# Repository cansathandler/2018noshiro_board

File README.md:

# 2018noshiro_board
2018年の能代で使用した基板

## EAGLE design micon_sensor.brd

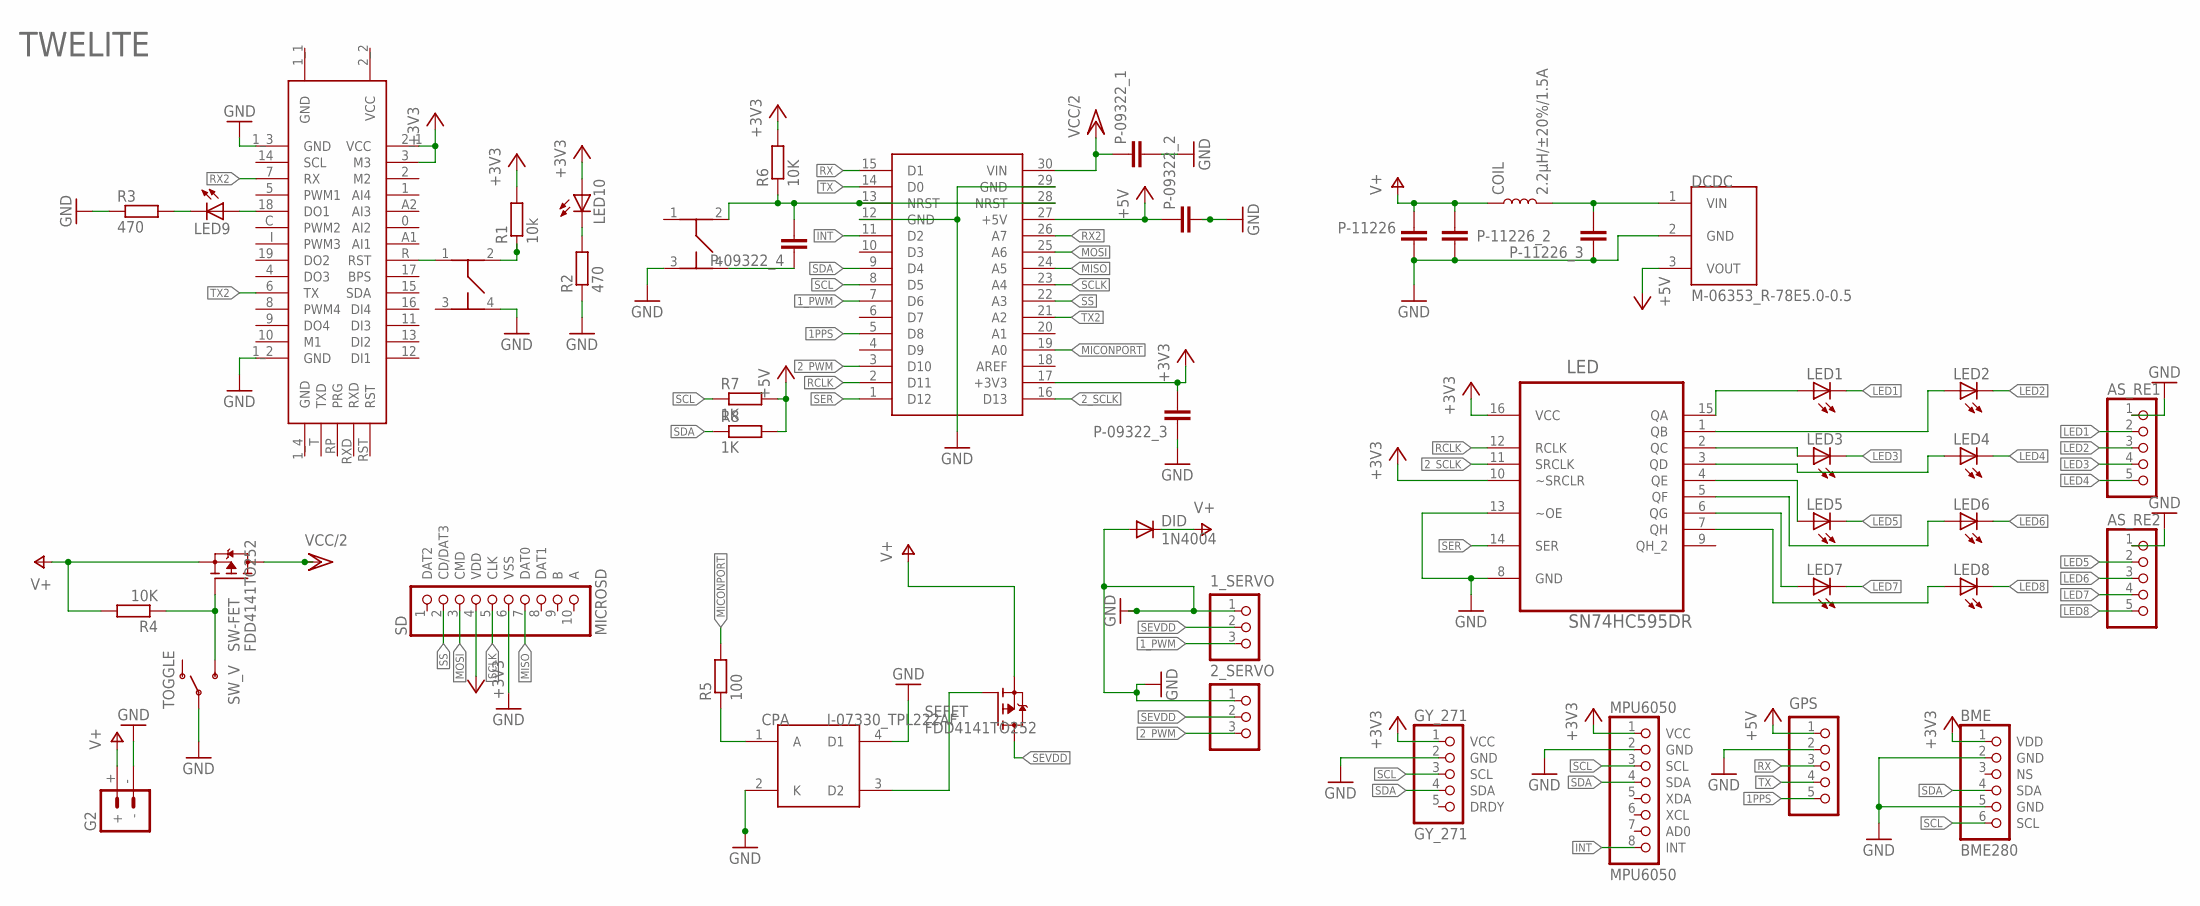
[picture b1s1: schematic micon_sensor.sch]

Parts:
1_SERVO, 2_SERVO: B3B-XH-A
AS_RE1, AS_RE2: PINHD-1X5; 1X05
BME: BME280; 1X06
COIL: 2.2µH/±20%/1.5A; INDUCTOR_2.2UH
CPA: I-07330_TPL222AF; TLP222AF
DCDC: M-06353_R-78E5.0-0.5; R-78E5.0-0.5
DID: 1N4004; DO41-10
G2: BATTERY_CONN_DEANS; DEANS
GPS: B5B-XH-A
GY_271: GY_271; 1X05
LED: SN74HC595DR; SOIC127P600X175-16N
LED1, LED2, LED3, LED4, LED5, LED6, LED7, LED8, LED9, LED10: LEDCHIP-LED0603; CHIP-LED0603
MPU6050: MPU6050; 1X08
P-09322_1, P-09322_2, P-09322_3, P-09322_4, P-11226, P-11226_2, P-11226_3: C-EUC0805; C0805
R1: 10k; R0805
R2, R3: 470; R0805
R4, R6: 10K; R0805
R5: 100; R0805
R7, R8: 1K; R0805
SD: MICROSD; 1X10
SEFET: FDD4141TO252; TO252
SW-FET: FDD4141TO252; TO252
SW_MI: SWITCH
SW_V: TOGGLE; 320-916
TWE_SW: SWITCH
U$1: TWELITE; TWELITE_DIP
U$3: STM32F303K8

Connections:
1PPS: GPS.5, U$3.5 (D8)
1_PWM: 1_SERVO.3, U$3.7 (D6)
2_PWM: 2_SERVO.3, U$3.3 (D10)
2_SCLK: LED.11 (SRCLK), U$3.16 (D13)
+3V3: BME.1 (VDD), GY_271.1 (VCC), LED.10 (~SRCLR), LED.16 (VCC), LED10.A, MPU6050.1 (VCC), P-09322_3.2, R1.2, R6.2, SD.4 (VDD), U$1.2_1 (VCC), U$1.3 (M3), U$3.17 (+3V3)
+5V: DCDC.3 (VOUT), GPS.1, P-09322_2.1, R7.2, R8.2, U$3.27 (+5V)
AREF: U$3.18 (AREF)
GND: 1_SERVO.1, 2_SERVO.1, AS_RE1.1, AS_RE2.1, BME.2 (GND), BME.5 (GND), CPA.2 (K), CPA.4 (D1), DCDC.2 (GND), DID.A, G2.-, GPS.2, GY_271.2 (GND), LED.8 (GND), LED.13 (~OE), MPU6050.2 (GND), P-09322_1.2, P-09322_2.2, P-09322_3.1, P-11226.1, P-11226_2.1, P-11226_3.1, R2.1, R3.1, SD.6 (VSS), SW_MI.3, SW_V.2, TWE_SW.4, U$1.1_2 (GND), U$1.1_3 (GND), U$3.12 (GND), U$3.29 (GND)
INT: MPU6050.8 (INT), U$3.11 (D2)
LED1: AS_RE1.2, LED1.C
LED2: AS_RE1.3, LED2.C
LED3: AS_RE1.4, LED3.C
LED4: AS_RE1.5, LED4.C
LED5: AS_RE2.2, LED5.C
LED6: AS_RE2.3, LED6.C
LED7: AS_RE2.4, LED7.C
LED8: AS_RE2.5, LED8.C
MICONPORT: R5.2, U$3.19 (A0)
MISO: SD.7 (DAT0), U$3.24 (A5)
MOSI: SD.3 (CMD), U$3.25 (A6)
unnamed: COIL.P$2 (2), DCDC.1 (VIN), P-11226_3.2
unnamed: P-09322_4.2, R6.1, SW_MI.2, U$3.13 (NRST), U$3.28 (NRST)
unnamed: P-09322_4.1, SW_MI.4
unnamed: CPA.1 (A), R5.1
unnamed: CPA.3 (D2), SEFET.1 (G)
unnamed: LED.15 (QA), LED1.A
unnamed: LED.1 (QB), LED2.A
unnamed: LED.2 (QC), LED3.A
unnamed: LED.3 (QD), LED4.A
unnamed: LED9.A, U$1.18 (DO1)
unnamed: LED.4 (QE), LED5.A
unnamed: LED.5 (QF), LED6.A
unnamed: LED.6 (QG), LED7.A
unnamed: LED.7 (QH), LED8.A
unnamed: LED9.C, R3.2
unnamed: LED10.C, R2.2
unnamed: TWE_SW.1, U$1.R (RST)
unnamed: R1.1, TWE_SW.2
unnamed: R4.1, SW-FET.1 (G), SW_V.3
RCLK: LED.12 (RCLK), U$3.2 (D11)
RX: GPS.3, U$3.15 (D1)
RX2: U$1.7 (RX), U$3.26 (A7)
SCL: BME.6 (SCL), GY_271.3 (SCL), MPU6050.3 (SCL), R7.1, U$3.8 (D5)
SCLK: SD.5 (CLK), U$3.23 (A4)
SDA: BME.4 (SDA), GY_271.4 (SDA), MPU6050.4 (SDA), R8.1, U$3.9 (D4)
SER: LED.14 (SER), U$3.1 (D12)
SEVDD: 1_SERVO.2, 2_SERVO.2, SEFET.3 (D)
SS: SD.2 (CD/DAT3), U$3.22 (A3)
TX: GPS.4, U$3.14 (D0)
TX2: U$1.6 (TX), U$3.21 (A2)
V+: COIL.P$1 (1), DID.C, G2.+, P-11226.2, P-11226_2.2, R4.2, SEFET.2 (S), SW-FET.2 (S)
VCC/2: P-09322_1.1, SW-FET.3 (D), U$3.30 (VIN)

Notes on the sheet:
TWELITE

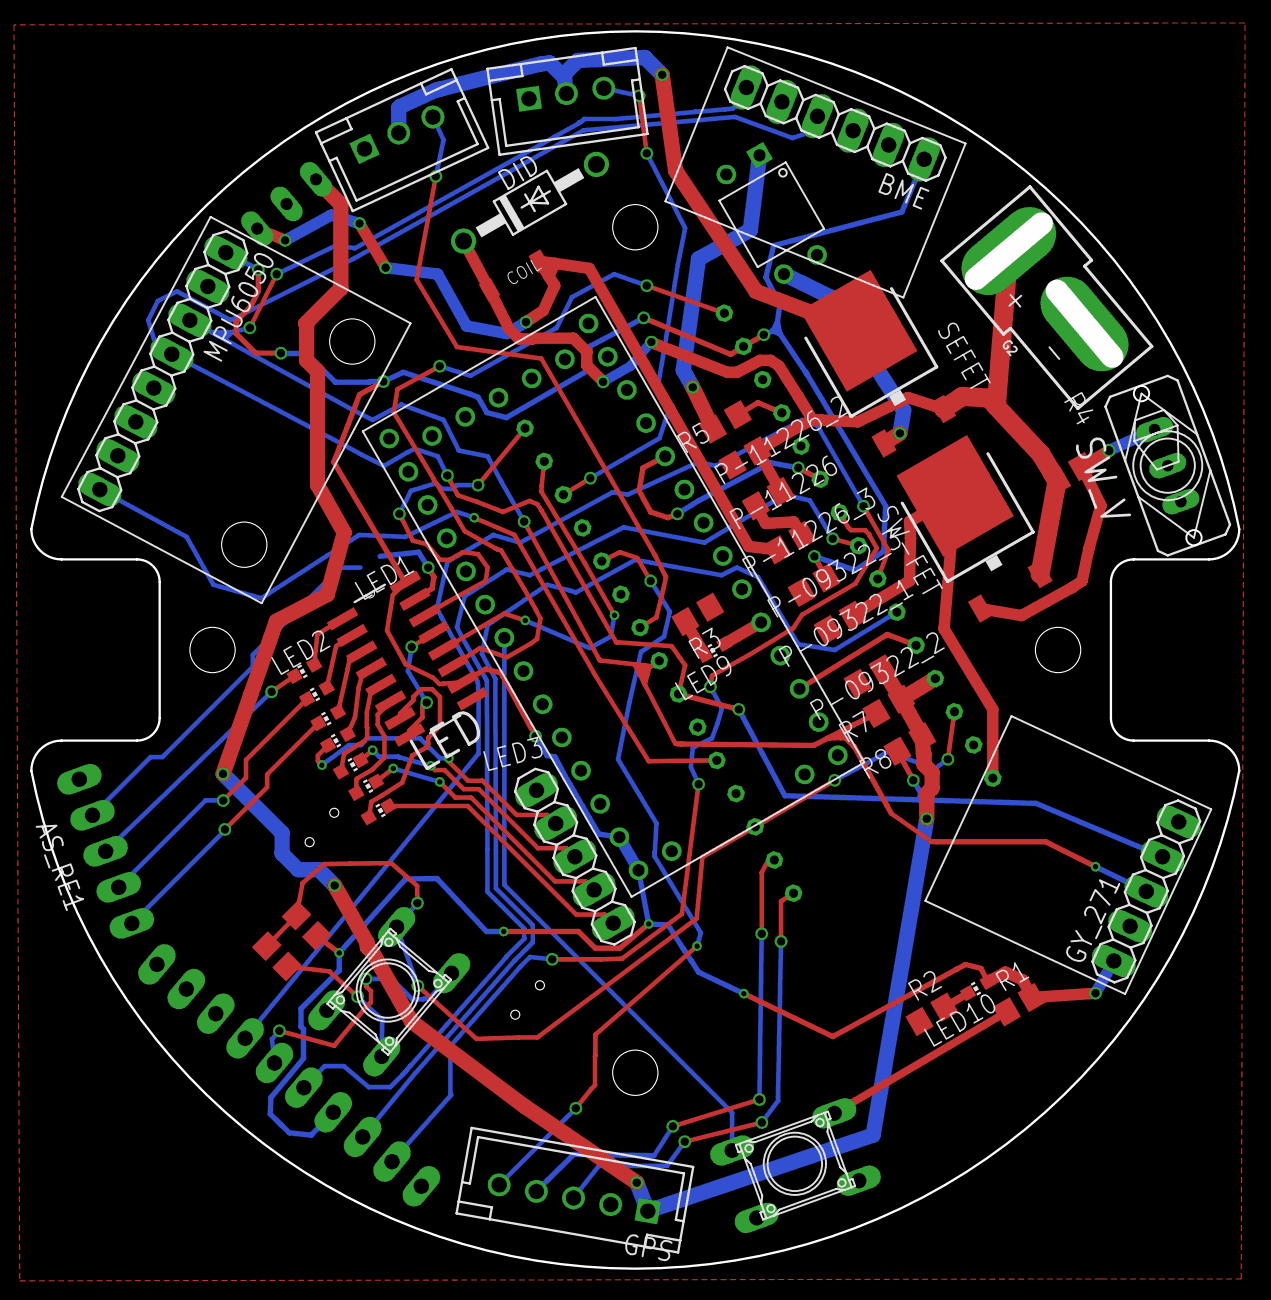
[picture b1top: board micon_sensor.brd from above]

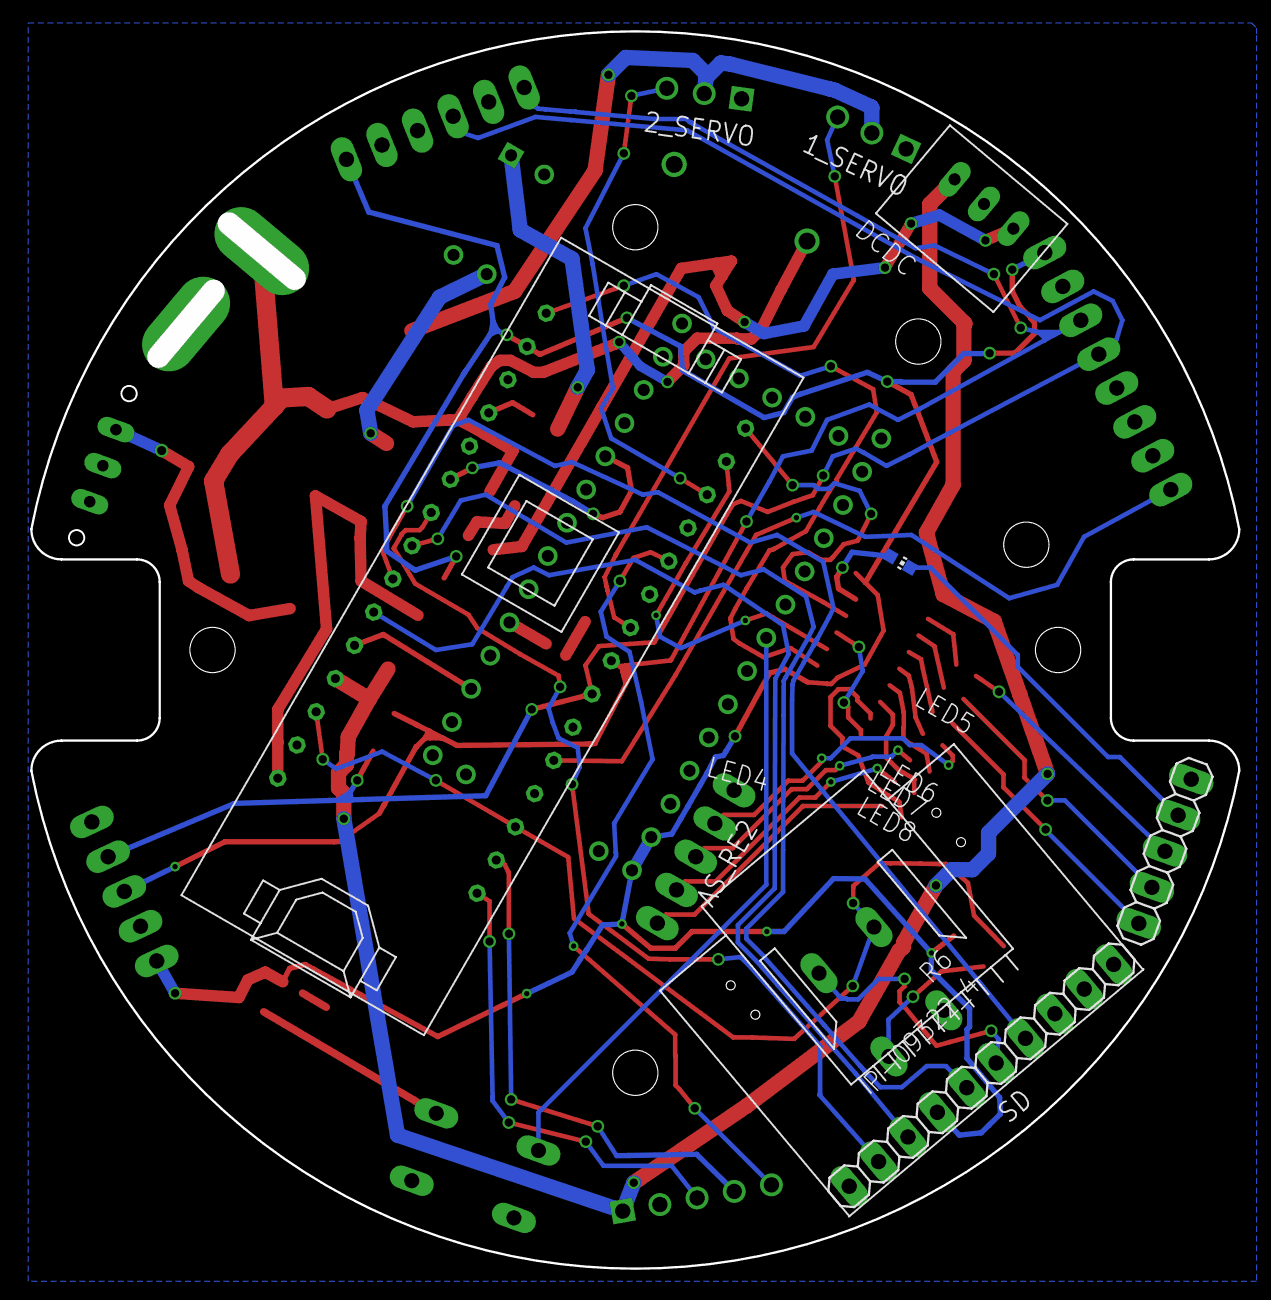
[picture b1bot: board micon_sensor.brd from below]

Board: 2 copper layers, 78.7 x 80.6 mm, 47 parts (5 on the bottom side), 51 nets.

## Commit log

2018-09-03 no message

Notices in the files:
parts and their libraries:
SparkFun-Connectors: Licensing: Creative Commons ShareAlike 4.0 International - https://creativecommons.org/licenses/by-sa/4.0
